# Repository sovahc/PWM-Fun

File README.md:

# PWM-Fun
PWM fan controller for water cooled PC

I didn't find the fan controller cheap and cute, so I made it myself.

For building minimal LCD version of this project you need:
* PCB (use Kicad to export gerber files for manufacturing)
* 170x320 SPI LCD (they are cheap and slow)
* ATMega328 microcontroller
* 2.54mm single row 8 pin male + female connector (I recommend short L7.5 version)
* 2x SMD 10k resistor (R1, R2)
* 7x SMD 220 Ohm resistor (R3 - R9)
* SMD 100 nF capacitor (C1)
* SMD(or not) 4.7 uF capacitor (C2)
* 7x angled PC Fan connector  
* M2.5 screws and nuts for mounting.
* SATA to Molex adapter (Not Molex to SATA!)

Equipment:
* Any AVR programmer (You can use any usb arduino board with sketch ArduinoISP, don't forget to press "Upload Using Programmer")
* Good soldering iron recomended.

You can add buzzer and 500 Ohm resistor if you like.

You can add WS2812 strip if you like.

You can use the ATmega internal oscillator if you are not using the WS2812.

Don't forget to short J1 if you not use U2 (probably you don't need U2)

The fans speed is controlled by the thermal sensor 1. The thermal sensor 2 is set to 50°C alarm. I use it to control the temperature of 12VHPWR connector 🩹

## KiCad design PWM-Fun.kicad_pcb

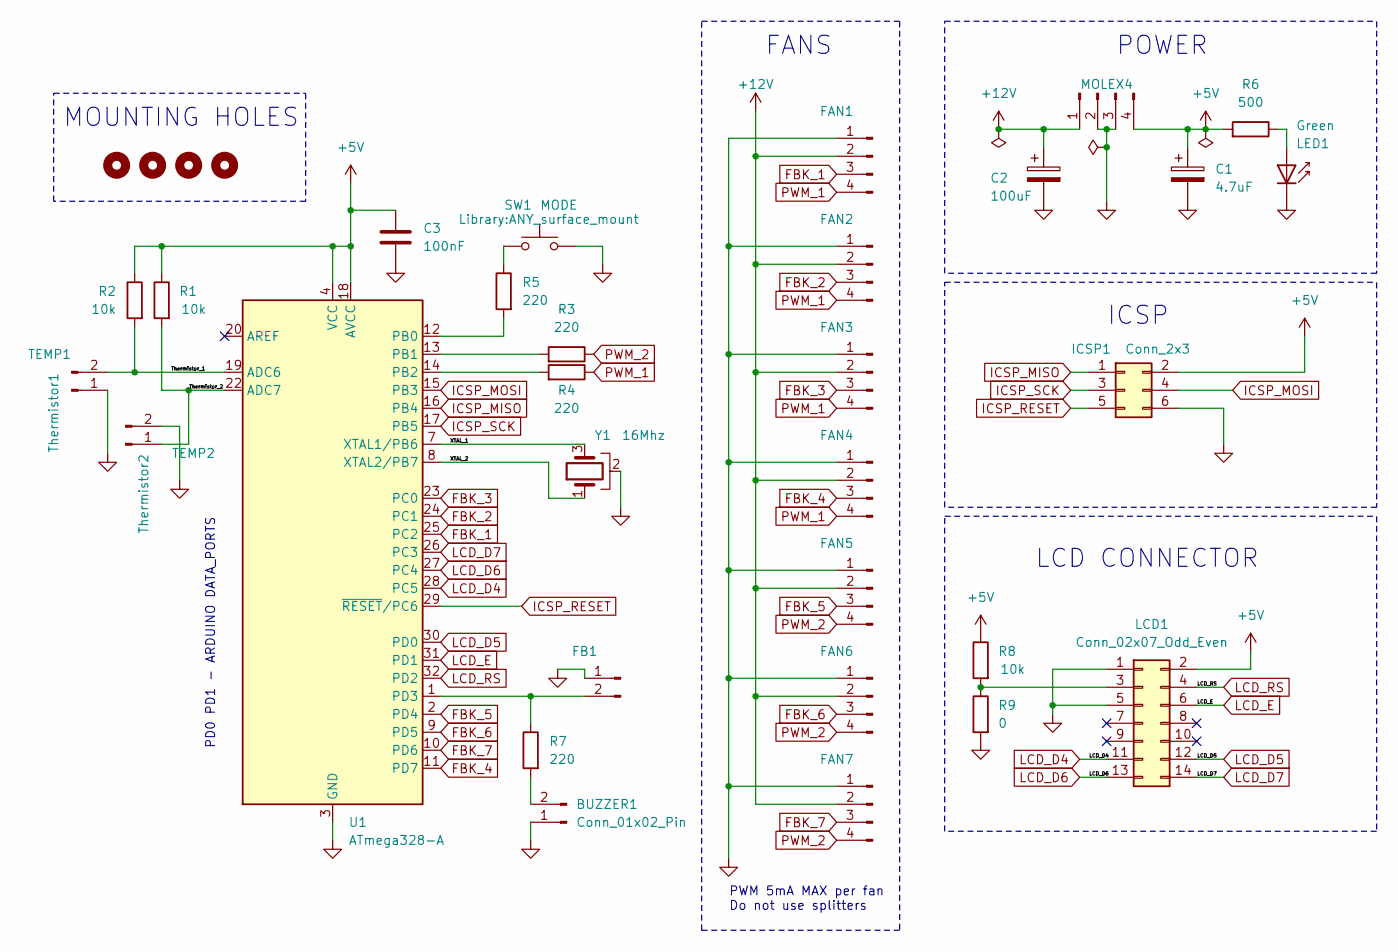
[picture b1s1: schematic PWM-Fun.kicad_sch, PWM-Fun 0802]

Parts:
BUZZER1: Conn_01x02_Pin; My_buzzer
C1: 4.7uF; Multicap
C2: 100uF; Multicap
C3: 100nF; C_0805_2012Metric_Pad1.18x1.45mm_HandSolder
FAN1, FAN2, FAN3, FAN4, FAN5, FAN6, FAN7: FanPinHeader_1x04_P2.54mm_Vertical_custom
FB1: TO_PC; PinSocket_1x02_P2.54mm_Vertical
H1, H2, H3, H4: MountingHole_Pad; Slot 2.5x1.27
ICSP1: Conn_2x3; PinHeader_2x03_P2.54mm_Horizontal
LCD1: Conn_02x07_Odd_Even; LCD_Connector_2x07_P2.54mm_Vertical
LED1: Green; ANY_surface_mount
MOLEX4: Conn_01x04_Pin; SolderWire-1-2_compact
R1, R2, R8: 10k; R_0805_2012Metric_Pad1.20x1.40mm_HandSolder
R3, R4, R5, R7: 220; R_0805_2012Metric_Pad1.20x1.40mm_HandSolder
R6: 500; R_0805_2012Metric_Pad1.20x1.40mm_HandSolder
R9: 0; R_0805_2012Metric_Pad1.20x1.40mm_HandSolder
SW1: MODE; ANY_surface_mount
TEMP1: Thermistor1; PinHeader_1x02_P2.54mm_Horizontal
TEMP2: Thermistor2; PinHeader_1x02_P2.54mm_Horizontal
U1: ATmega328-A; TQFP-32_7x7mm_P0.8mm
Y1: 16Mhz; Resonator_SMD_Murata_CSTxExxV-3Pin_3.0x1.1mm_HandSoldering

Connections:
+5V: C1.1, C3.1, ICSP1.2, LCD1.2, MOLEX4.4, R1.1, R2.1, R6.2, R8.1, U1.4 (VCC), U1.6 (VCC), U1.18 (AVCC)
+12V: C2.1, FAN1.2, FAN2.2, FAN3.2, FAN4.2, FAN5.2, FAN6.2, FAN7.2, MOLEX4.1
/Thermistor_1: R2.2, TEMP1.2, U1.19 (ADC6)
/Thermistor_2: R1.2, TEMP2.1, U1.22 (ADC7)
/XTAL_1: U1.7 (XTAL1/PB6), Y1.3
/XTAL_2: U1.8 (XTAL2/PB7), Y1.1
FBK_1: FAN1.3, U1.25 (PC2)
FBK_2: FAN2.3, U1.24 (PC1)
FBK_3: FAN3.3, U1.23 (PC0)
FBK_4: FAN4.3, U1.11 (PD7)
FBK_5: FAN5.3, U1.2 (PD4)
FBK_6: FAN6.3, U1.9 (PD5)
FBK_7: FAN7.3, U1.10 (PD6)
GND: BUZZER1.1, C1.2, C2.2, C3.2, FAN1.1, FAN2.1, FAN3.1, FAN4.1, FAN5.1, FAN6.1, FAN7.1, FB1.1, ICSP1.6, LCD1.1, LCD1.5, LED1.1 (K), MOLEX4.2, MOLEX4.3, R9.2, SW1.2, TEMP1.1, TEMP2.2, U1.3 (GND), U1.5 (GND), U1.21 (GND), Y1.2
ICSP_MISO: ICSP1.1, U1.16 (PB4)
ICSP_MOSI: ICSP1.4, U1.15 (PB3)
ICSP_RESET: ICSP1.5, U1.29 (~RESET/PC6)
ICSP_SCK: ICSP1.3, U1.17 (PB5)
LCD_D4: LCD1.11, U1.28 (PC5)
LCD_D5: LCD1.12, U1.30 (PD0)
LCD_D6: LCD1.13, U1.27 (PC4)
LCD_D7: LCD1.14, U1.26 (PC3)
LCD_E: LCD1.6, U1.31 (PD1)
LCD_RS: LCD1.4, U1.32 (PD2)
unnamed: BUZZER1.2, R7.2
unnamed: FB1.2, R7.1, U1.1 (PD3)
unnamed: LCD1.3, R8.2, R9.1
unnamed: LED1.2 (A), R6.1
unnamed: R5.1, SW1.1
unnamed: R5.2, U1.12 (PB0)
unnamed: R3.2, U1.13 (PB1)
unnamed: R4.2, U1.14 (PB2)
PWM_1: FAN1.4, FAN2.4, FAN3.4, FAN4.4, R4.1
PWM_2: FAN5.4, FAN6.4, FAN7.4, R3.1

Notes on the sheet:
MOUNTING HOLES
FANS
ICSP
PD0 PD1 - ARDUINO DATA_PORTS
LCD CONNECTOR
PWM 5mA MAX per fan Do not use splitters
POWER

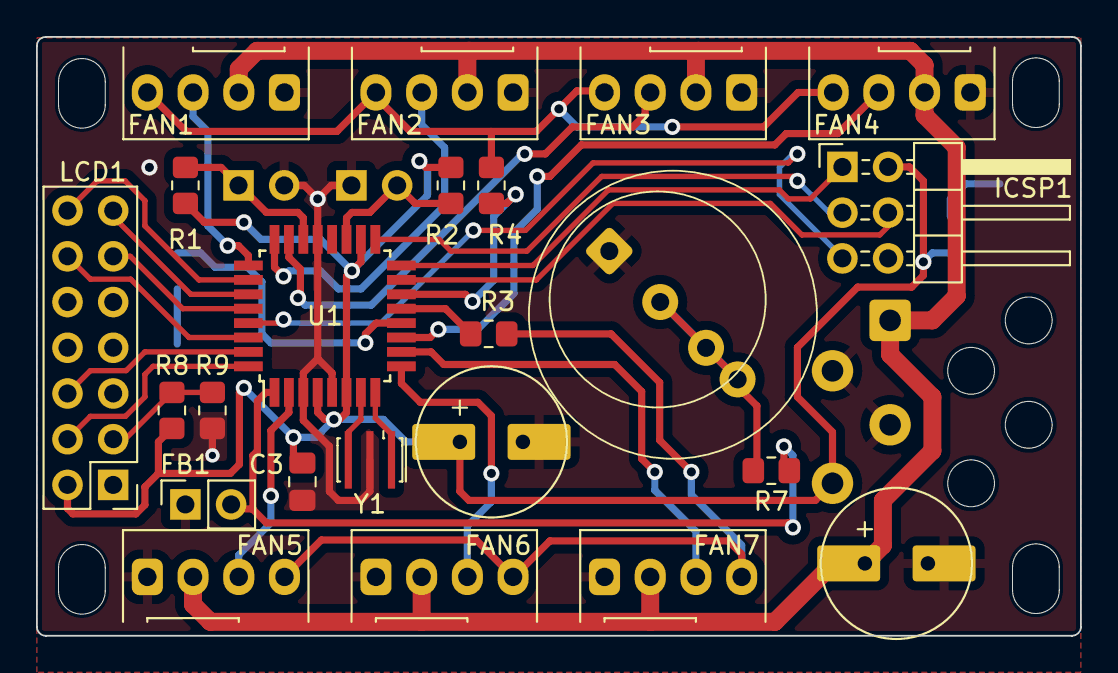
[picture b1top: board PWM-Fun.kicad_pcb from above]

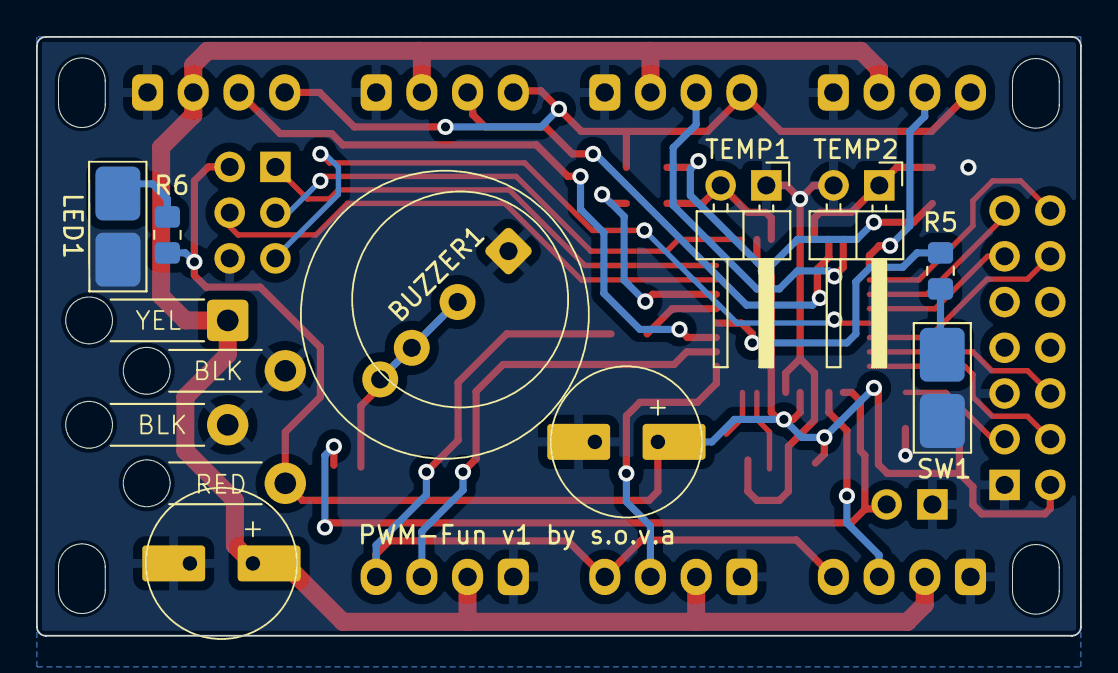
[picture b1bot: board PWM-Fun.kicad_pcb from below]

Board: 2 copper layers, 58.0 x 33.3 mm, 34 parts (8 on the bottom side), 34 nets.

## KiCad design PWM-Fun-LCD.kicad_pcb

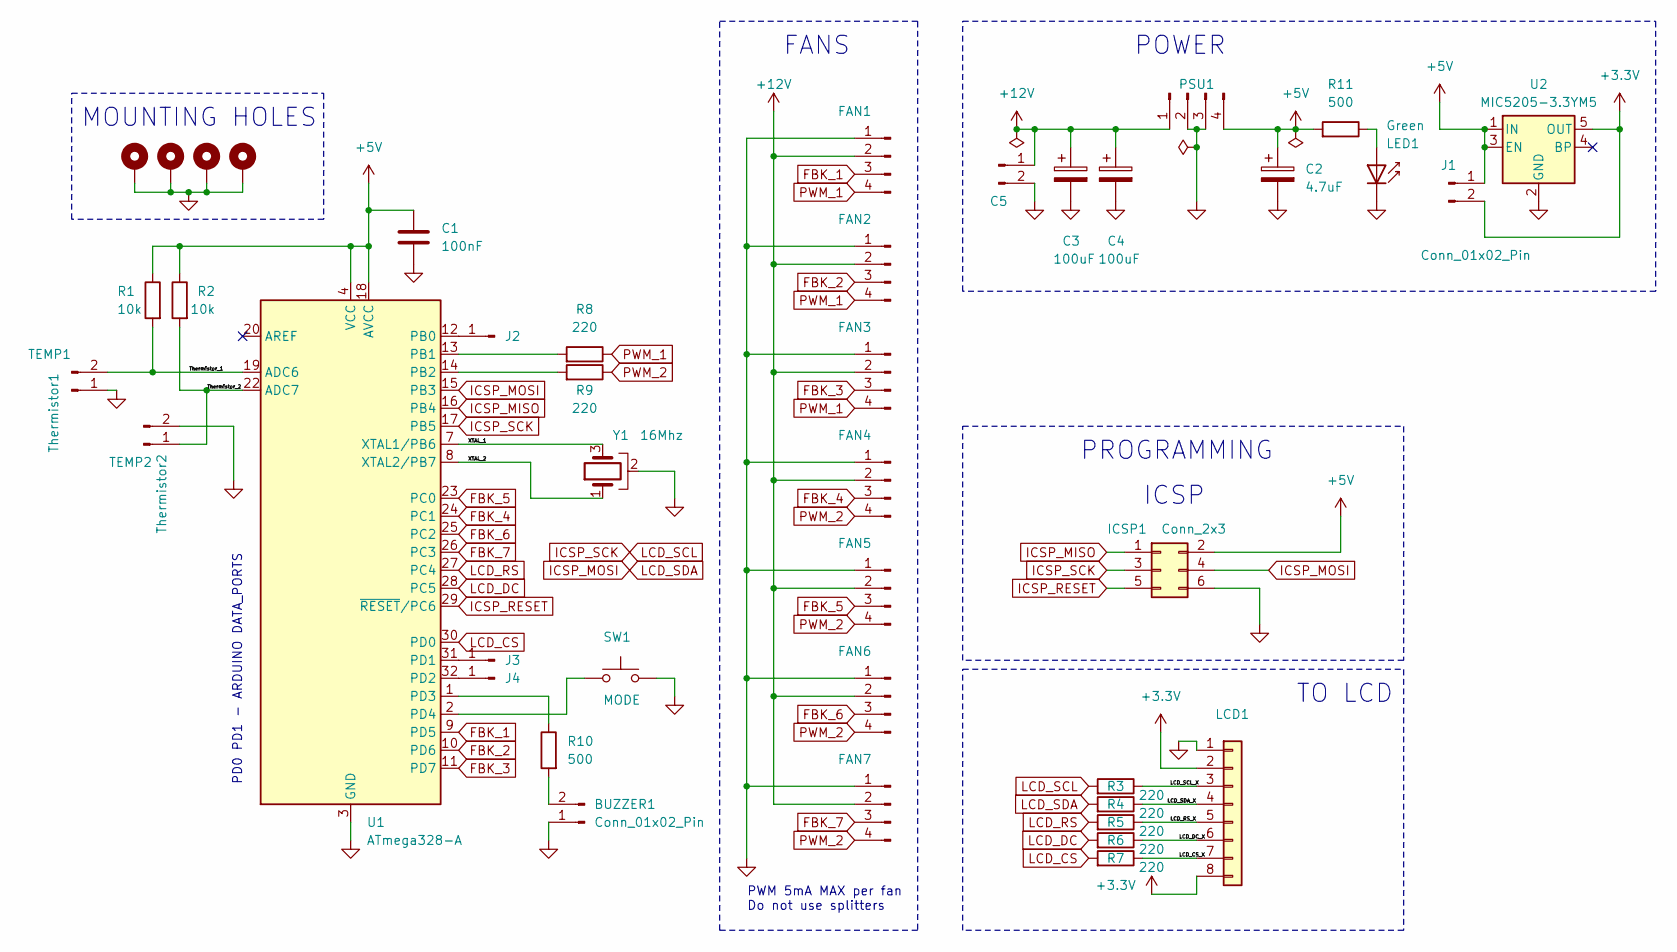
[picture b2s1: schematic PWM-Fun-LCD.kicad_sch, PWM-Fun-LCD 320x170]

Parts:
BUZZER1: Conn_01x02_Pin; My_buzzer
C1: 100nF; C_0805_2012Metric_Pad1.18x1.45mm_HandSolder
C2: 4.7uF; Multicap
C3, C4: 100uF; CP_Elec_6.3x3.9
C5: TO_PC; PinSocket_1x02_P2.54mm_Vertical
FAN1, FAN2, FAN3, FAN4, FAN5, FAN6, FAN7: FanPinHeader_1x04_P2.54mm_Vertical_custom
H1, H2, H3, H4: MountingHole_Pad; MountingHole_2.2mm_M2_Pad
ICSP1: Conn_2x3; PinHeader_2x03_P2.54mm_Horizontal
J1: Conn_01x02_Pin; SolderJumper-2_P1.3mm_Open_TrianglePad1.0x1.5mm
J2, J3, J4: Unused; TestPoint_Pad_D2.0mm
LCD1: PinSocket_1x08_P2.54mm_Vertical
LED1: Green; ANY_surface_mount
PSU1: Conn_01x04_Pin; SolderWire-1-2_compact
R1, R2: 10k; R_0805_2012Metric_Pad1.20x1.40mm_HandSolder
R3, R4, R5, R6, R7, R8, R9: 220; R_0805_2012Metric_Pad1.20x1.40mm_HandSolder
R10, R11: 500; R_0805_2012Metric_Pad1.20x1.40mm_HandSolder
SW1: MODE; ANY_surface_mount
TEMP1: Thermistor1; my_PinHeader_1x02_P2.54mm_Horizontal
TEMP2: Thermistor2; my_PinHeader_1x02_P2.54mm_Horizontal
U1: ATmega328-A; TQFP-32_7x7mm_P0.8mm
U2: MIC5205-3.3YM5; SOT-23-5
Y1: 16Mhz; Resonator_SMD_Murata_CSTxExxV-3Pin_3.0x1.1mm_HandSoldering

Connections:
+3.3V: J1.2, LCD1.2, LCD1.8, U2.5 (OUT)
+5V: C1.1, C2.1, ICSP1.2, J1.1, PSU1.4, R1.1, R2.1, R11.2, U1.4 (VCC), U1.6 (VCC), U1.18 (AVCC), U2.1 (IN), U2.3 (EN)
+12V: C3.1, C4.1, C5.1, FAN1.2, FAN2.2, FAN3.2, FAN4.2, FAN5.2, FAN6.2, FAN7.2, PSU1.1
/LCD_CS_X: LCD1.7, R7.1
/LCD_DC_X: LCD1.6, R6.1
/LCD_RS_X: LCD1.5, R5.1
/LCD_SCL_X: LCD1.3, R3.1
/LCD_SDA_X: LCD1.4, R4.1
/Thermistor_1: R1.2, TEMP1.2, U1.19 (ADC6)
/Thermistor_2: R2.2, TEMP2.1, U1.22 (ADC7)
/XTAL_1: U1.7 (XTAL1/PB6), Y1.3
/XTAL_2: U1.8 (XTAL2/PB7), Y1.1
FBK_1: FAN1.3, U1.9 (PD5)
FBK_2: FAN2.3, U1.10 (PD6)
FBK_3: FAN3.3, U1.11 (PD7)
FBK_4: FAN4.3, U1.24 (PC1)
FBK_5: FAN5.3, U1.23 (PC0)
FBK_6: FAN6.3, U1.25 (PC2)
FBK_7: FAN7.3, U1.26 (PC3)
GND: BUZZER1.1, C1.2, C2.2, C3.2, C4.2, C5.2, FAN1.1, FAN2.1, FAN3.1, FAN4.1, FAN5.1, FAN6.1, FAN7.1, H1.1, H2.1, H3.1, H4.1, ICSP1.6, LCD1.1, LED1.1 (K), PSU1.2, PSU1.3, SW1.2, TEMP1.1, TEMP2.2, U1.3 (GND), U1.5 (GND), U1.21 (GND), U2.2 (GND), Y1.2
ICSP_MISO: ICSP1.1, U1.16 (PB4)
ICSP_MOSI: ICSP1.4, R4.2, U1.15 (PB3)
ICSP_RESET: ICSP1.5, U1.29 (~RESET/PC6)
ICSP_SCK: ICSP1.3, R3.2, U1.17 (PB5)
LCD_CS: R7.2, U1.30 (PD0)
LCD_DC: R6.2, U1.28 (PC5)
LCD_RS: R5.2, U1.27 (PC4)
unnamed: BUZZER1.2, R10.2
unnamed: J2.1, U1.12 (PB0)
unnamed: J3.1, U1.31 (PD1)
unnamed: J4.1, U1.32 (PD2)
unnamed: LED1.2 (A), R11.1
unnamed: R8.2, U1.13 (PB1)
unnamed: R9.2, U1.14 (PB2)
unnamed: R10.1, U1.1 (PD3)
unnamed: SW1.1, U1.2 (PD4)
PWM_1: FAN1.4, FAN2.4, FAN3.4, R8.1
PWM_2: FAN4.4, FAN5.4, FAN6.4, FAN7.4, R9.1

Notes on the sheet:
MOUNTING HOLES
FANS
PROGRAMMING
ICSP
PD0 PD1 - ARDUINO DATA_PORTS
TO LCD
PWM 5mA MAX per fan Do not use splitters
POWER

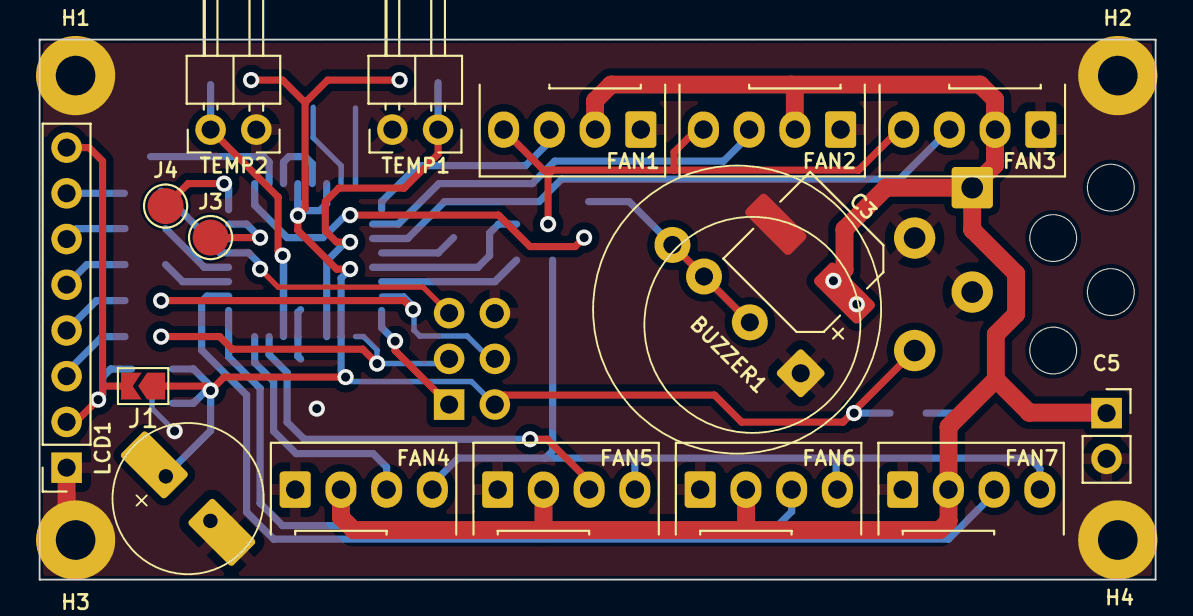
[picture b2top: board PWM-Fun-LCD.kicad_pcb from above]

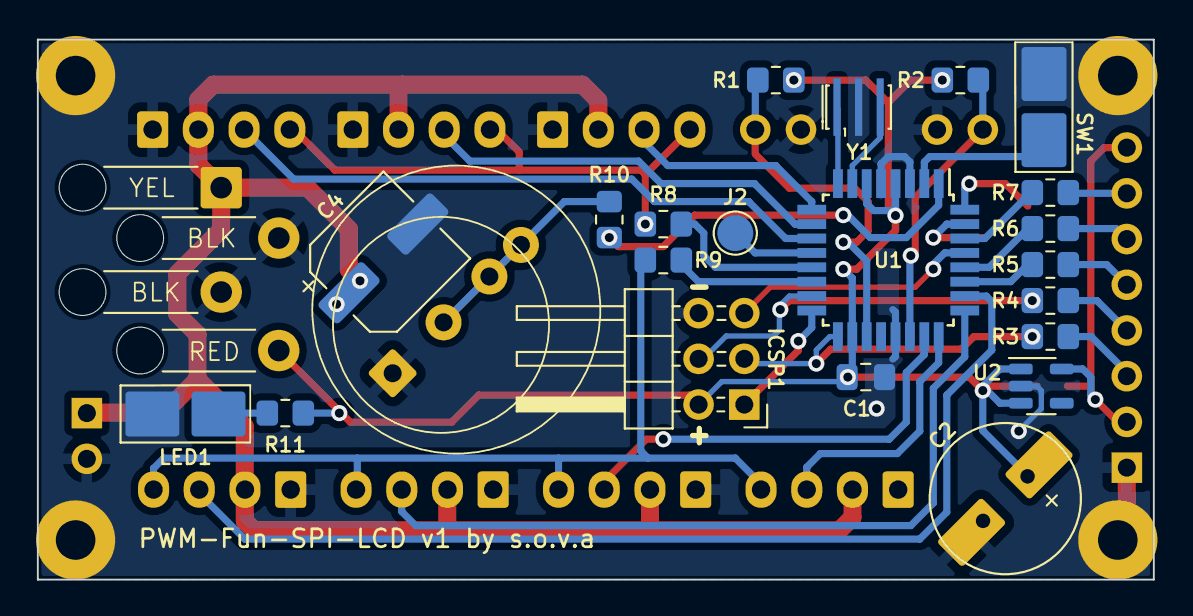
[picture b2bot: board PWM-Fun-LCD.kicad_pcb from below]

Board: 2 copper layers, 62.0 x 30.0 mm, 42 parts (22 on the bottom side), 38 nets.

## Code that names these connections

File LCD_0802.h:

#define FAN_FEEDBACK_PINS_C_COUNT 3
#define FAN_FEEDBACK_PINS_C { 16, 15, 14 }
#define FAN_FEEDBACK_PINS_D_COUNT 4
#define FAN_FEEDBACK_PINS_D { 7, 4, 5, 6 }

// LCD 0802 pins:
static const int LCD_RS = 2;
static const int LCD_E  = 1;
static const int LCD_D4 = 19;
static const int LCD_D5 = 0;
static const int LCD_D6 = 18;
static const int LCD_D7 = 17;

#include <LiquidCrystal.h>

LiquidCrystal lcd_move_me_to_class(LCD_RS, LCD_E, LCD_D4, LCD_D5, LCD_D6, LCD_D7);

class My_display
{
    static constexpr LiquidCrystal& lcd = lcd_move_me_to_class;

    static const byte celsius_character = 0;
    static const byte fan_character = 1;

  public:
    static void initialize()
    {
      delay(100); // Wait for display is powered up.
      lcd.begin(8, 2);

      byte celsius_character_mask[] PROGMEM = {
        B11100,
        B10100,
        B11100,
        B00000,
        B00000,
        B00000,
        B00000,
        B00000
      };

      byte fan_character_mask[] PROGMEM = {
        B01100,
        B01100,
        B00101,
        B11011,
        B11011,
        B10100,
        B00110,
        B00110
      };

      lcd.createChar(celsius_character, celsius_character_mask);
      lcd.createChar(fan_character, fan_character_mask);

      /*
        // Custom characters for the progress bar
        uint8_t bars[] = {B10000, B11000, B11100, B11110, B11111};
        uint8_t character[8];
        for (uint8_t i = 0; i < 5; ++i) {
        for (uint8_t j = 0; j < 8; ++j) character[j] = bars[i];
        lcd.createChar(i, character);
        }*/

      lcd.setCursor(0, 0);
      lcd.print("Water   ");
      lcd.setCursor(0, 1);
      lcd.print("VHPWR   ");
    }

    static void print_temperature(int line, float t, bool none)
    {
      lcd.setCursor(0, line);

      if(none)
      { lcd.print("NONE   ");
      }
      else
      { lcd.print(t, 1);
        lcd.write(celsius_character);
        lcd.print("C ");
      }
    }

    static void print_fans_count(int count)
    {
      lcd.setCursor(7, 0);
      lcd.write(fan_character);
      lcd.setCursor(7, 1);
      lcd.print(count);
    }

    static void flash_led(int delay_ms, int count)
    {
      for (int i = 0; i < count; ++i)
      { digitalWrite(LED_BUILTIN, HIGH);
        delay(delay_ms);
        digitalWrite(LED_BUILTIN, LOW);
        delay(delay_ms);
      }
    }

    static void display_error(const char* m1, const char* m2)
    { lcd.setCursor(0, 0);
      lcd.print(m1);
      lcd.setCursor(0, 1);
      lcd.print("        ");

      flash_led(50, 3);

      lcd.setCursor(0, 0);
      lcd.print("        ");
      lcd.setCursor(0, 1);
      lcd.print(m2);

      flash_led(50, 3);
    }
};
